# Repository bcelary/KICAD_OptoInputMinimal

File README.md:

# OptoInputMinimal
This repo contains a Kicad project of a very primitive opto-isolated binary input for arduino. It contains 8 inputs. The bill of materials as follows:

* Input R: 1K
* Output R: 4.7K
* Optocoupler: 4n25
* 3.5mm screw terminal blocks (e.g. 6pcs of 2 pin and 3pcs of 3 pin)

# Schematic

# 3D view

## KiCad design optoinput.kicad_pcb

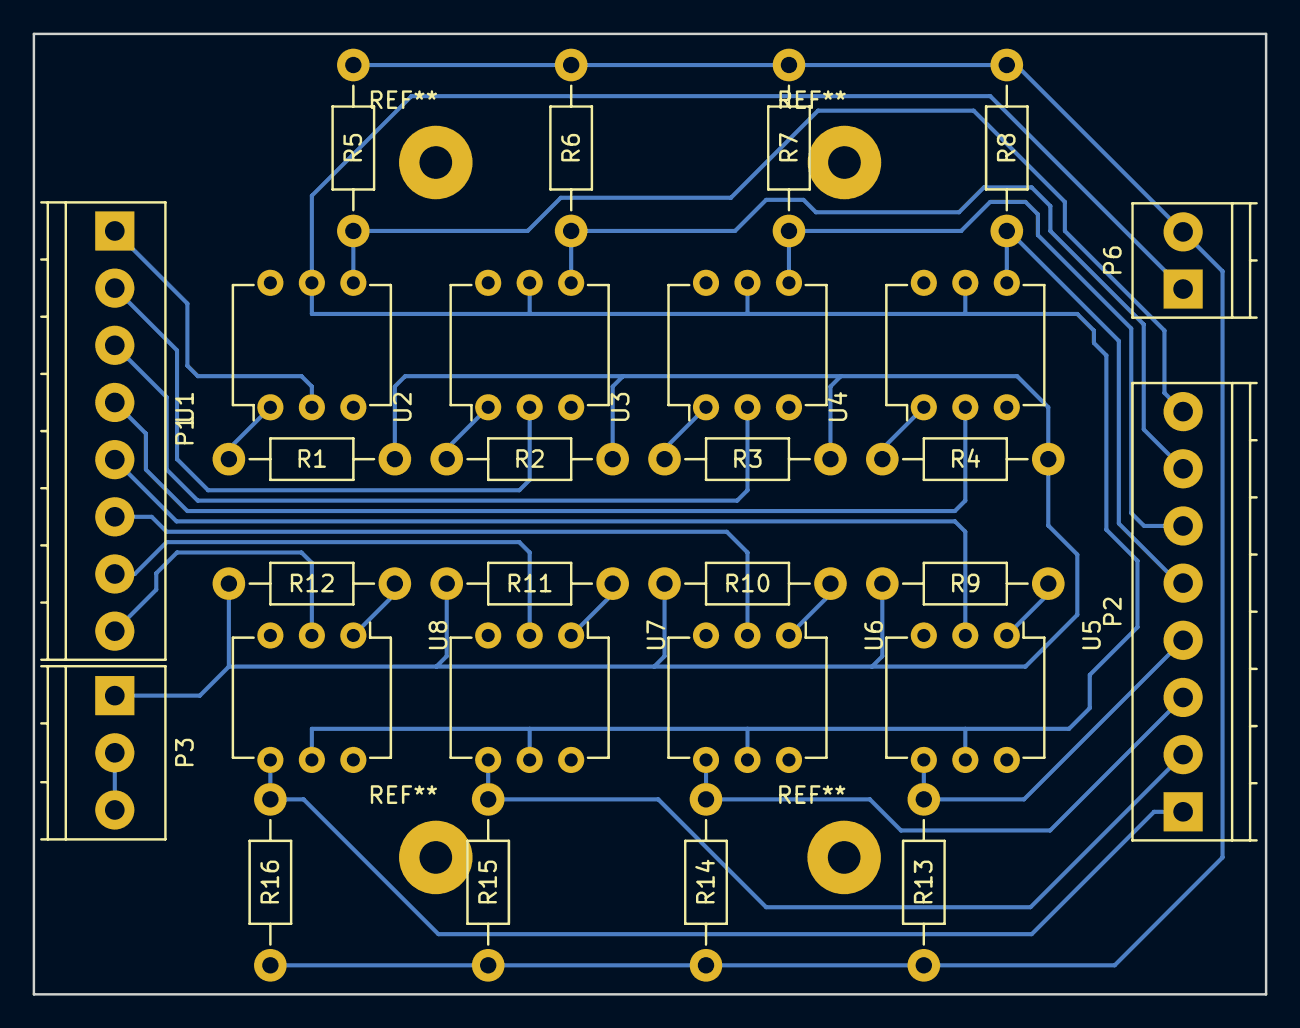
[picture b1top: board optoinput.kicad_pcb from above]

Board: 2 copper layers, 75.4 x 58.8 mm, 28 parts (0 on the bottom side), 28 nets.

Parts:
P1, P2: CONN_01X08; TerminalBlock_Pheonix_PT-3.5mm_8pol
P3: CONN_01X03; TerminalBlock_Pheonix_PT-3.5mm_3pol
P6: CONN_01X02; TerminalBlock_Pheonix_PT-3.5mm_2pol
R1, R2, R3, R4, R5, R6, R7, R8, R9, R10, R11, R12, R13, R14, R15, R16: R; Resistor_Horizontal_RM10mm
U1, U2, U3, U4, U5, U6, U7, U8: 4N25; DIP-6_W7.62mm

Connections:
+12V: P3.1, R1.1, R2.1, R3.1, R4.1, R9.1, R10.1, R11.1, R12.1
/X1: P1.1, U1.2
/X2: P1.2, U2.2
/X3: P1.3, U3.2
/X4: P1.4, U4.2
/X5: P1.5, U5.2
/X6: P1.6, U6.2
/X7: P1.7, U7.2
/X8: P1.8, U8.2
/Y1: P2.8, R5.1, U1.4
/Y2: P2.7, R6.1, U2.4
/Y3: P2.6, R7.1, U3.4
/Y4: P2.5, R8.1, U4.4
/Y5: P2.4, R13.1, U5.4
/Y6: P2.3, R14.1, U6.4
/Y7: P2.2, R15.1, U7.4
/Y8: P2.1, R16.1, U8.4
GND: P6.2, R5.2, R6.2, R7.2, R8.2, R13.2, R14.2, R15.2, R16.2
GNDA: P3.2, P3.3
unnamed: R1.2, U1.1
unnamed: R2.2, U2.1
unnamed: R3.2, U3.1
unnamed: R4.2, U4.1
unnamed: R9.2, U5.1
unnamed: R10.2, U6.1
unnamed: R11.2, U7.1
unnamed: R12.2, U8.1
VCC: P6.1, U1.5, U2.5, U3.5, U4.5, U5.5, U6.5, U7.5, U8.5

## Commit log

2016-04-01 initial pcb commit
2016-04-01 minor changes
2016-04-02 added images
2016-07-18 schema mods
2016-07-18 single layer mod
2016-07-18 moved tracks/zones to back layer
2016-07-18 removed fill zone, changed plot to PDF(mirrored), more separation between +12 and +5 zones
2016-07-18 changed to PS plot, clean up tracks
2016-07-18 updated 3d screenshot
2016-07-18 Added note about terminal blocks
2016-07-22 Change position for screw holes (25mm for DIN rail mounting)
